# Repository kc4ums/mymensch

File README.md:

# MyMENSCH APRS

A software TNC for WDC's MyMENSCH Rev-C board and a Kenwood TM-V71A. The MyMENSCH does all the packet work itself, with no external TNC: it builds APRS packets and sends them as 1200-baud audio through a small interface board on the radio's data port. The board's FPGA runs a W65C02 at 3.6864 MHz.

## Status

| Part | State |
|---|---|
| Transmit (`tnc/`): position beacons, periodic beacon, test tones, LEDs | Done. Passes the emulator test, including decoding its own audio. **Not yet tried on the board or on air.** |
| Radio interface: schematic and milled PCB (`hardware/`) | Done. The layout passes its clearance and connectivity checks. **Not yet cut.** |
| Receive: demodulate 1200-baud audio, decode packets | Next. The APRS decoder is ready in `tnc/aprs_decode/`. |
| Board hardware facts | Measured; see below. |
| W65C134SXB port (`tnc134/`) | **Runs on a real SXB**, loaded with `tools/sxb134`. It has a test mode (`T`) that prints 20 simulated South Georgia stations. Not yet on air. |
| Uploader (`tools/sxb134/`) | **Works on a real SXB** for loading RAM. Flash writing has been tested only on the emulator; the chip's ID was read on the board. |
| Text map (`tools/aprsmap/`) | **Works with the real SXB** in `tnc134`'s test mode. It can load the TNC itself (`--load`) and has a command line for TNC keys. |
| AMTOR station (`amtor/`) | Written for the W65C134SXB with a PS/2 keyboard, an LCD and a TS-480. Emulator only; its full test still has to be rerun. |

## Folders

| Folder | Contents |
|---|---|
| `tnc/` | The software TNC (transmit side). `tnc/aprs_decode/` holds the APRS decoder from the old PK-232 receiver, for the receive work. |
| `tnc134/` | The same software TNC ported to WDC's W65C134SXB: Port 5 I/O, the ROM monitor's console, 5 V. Includes the South Georgia test mode (`mk_sim.py`). |
| `amtor/` | An HF AMTOR (SITOR-B) message station for the W65C134SXB that needs no PC: a PS/2 keyboard, a 20x4 LCD and a Kenwood TS-480. It can be written into the SXB's flash so it starts at power-up. |
| `hardware/` | Radio interface schematic (`radio_interface.svg`), plus `pcb/`: the CNC-milled board's GRBL G-code, drawings and generator. |
| `hardware/c02board/` | C02COMM: an all-through-hole W65C02S board for these projects (RAM, flash, 2 VIAs, ACIA, two radio ports, LCD, PS/2, USB serial). It's a KiCad 10 project generated from `board.py`. Routed, DRC clean, Gerbers generated; not yet ordered or built. |
| `monitor/` | MMON, a machine-language monitor: dump and edit memory and I/O, load S19 files, run code, catch BRKs. |
| `probes/` | Small programs that test the board's hardware, and what they found. |
| `lib/` | `dbg.inc`: register and memory dump helpers to include in any program. |
| `tools/emu/` | The 65C02 emulator of the MyMENSCH that every test runs on. |
| `tools/sxb134/` | `sxb134.py`: loads, verifies and starts programs on a W65C134SXB through its ROM monitor (instead of EasySXB). It can also write the SXB's SST39SF010A flash (`--flash`). |
| `tools/aprsmap/` | `aprsmap.py`: APRS stations on an ASCII map in a text terminal, from a serial TNC, KISS, or Direwolf over TCP. It can load `tnc134` onto the SXB (`--load`), and `:` opens a command line to the TNC. |
| `docs/` | W65C165i1M08SA datasheet. |

## Building and loading

You need WDCTools (`C:\WDC\Tools\BIN` on the PATH) and WDC's uploader. Each program folder has a `mk_*.bat`.

For the W65C134SXB, use this repo's uploader instead (see `tools/sxb134/README.md`), or let the map load the TNC and start it:

```
python tools\sxb134\sxb134.py COM5 tnc134\tnc134.hex --go 2000 --term
python tools\aprsmap\aprsmap.py COM5 --load --send T --home 31.45,-83.51
```

For the MyMENSCH:

```
cd tnc
mk_tnc.bat
wdc_uploader_term.exe -d COM4 tnc.bin -m write -x -s 5 -t
```

Press RESET on the board when the uploader asks. The program then runs from RAM and its console appears in the uploader's terminal (Ctrl+] to quit). Programs live in RAM, so re-upload after every power cycle. Storing to flash (`-k`) fails on this board with "Clear Failed": the user-flash controller seems to be missing from the FPGA image (see below).

## First bench test (no radio)

1. Load `tnc.bin` as above. LED 0 should double-flash once a second. That shows Timer 1 and the program are running.
2. Press `1` for a test tone. J3-35 (PTT) should go high, and J3-37…43 (the DAC) should toggle. Any key stops it.
3. Then build the interface board (`hardware/pcb/README.md`) and follow "First time on the air" in `tnc/README.md`.

## Wiring to the MyMENSCH

Everything connects to **J3** (VIA_A port A):

| J3 pin | Signal |
|---|---|
| 29 | PA7: comparator output (RX audio) |
| 33 | PA5: radio SQC (optional) |
| 35 | PA4: PTT |
| 37, 39, 41, 43 | PA3-PA0: DAC bits 3-0 |
| 49 | +3V3 |
| 50 | GND |

On J3, pin 49 is +3V3 and pin 50 is GND, the reverse of J4.

## Tests

Every program has an emulator test; none needs the board:

```
python tnc/test_tnc.py
python tnc134/test_tnc134.py
python tools/sxb134/test_sxb134.py
python tools/sxb134/test_flash134.py
python tools/aprsmap/test_aprsmap.py
python amtor/test_amtor.py             (slow and memory-hungry; close other programs first)
python tnc/aprs_decode/run_tests.py
python monitor/test_mmon.py
python probes/test/test_regmap.py      (also test_probe, test_adcprobe, test_dbgdemo)
```

## What this board's FPGA image actually has

These were measured with the programs in `probes/`. They differ from the datasheet:

- **CPU clock:** 3.6864 MHz (the 14.7456 MHz oscillator divided by 4), with standard 65C02 cycle timing.
- **VIA_A:** works, with its ports on J3. **VIA_B and VIA_C are missing.**
- **VIA_A Timer 1 flag:** clears only when `$40` is written to the IFR, not when T1C-L is read.
- **Missing blocks:** the ADC, the multipliers and the chip ID are not in the image. That's why receive uses a comparator instead of the ADC.
- **User flash (UFM):** its registers at `$7FE0-$7FEC` read `00` (the write-protect register should reset to `1F`), and the uploader's `-k` fails with "Clear Failed". So it's most likely missing too, and programs can't be stored in flash.

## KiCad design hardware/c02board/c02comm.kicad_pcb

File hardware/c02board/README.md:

# C02COMM: a through-hole W65C02S board for the radio projects

This is a single board computer for the APRS TNC and the AMTOR station: a WDC W65C02S, RAM, flash, two radio ports, an LCD and keyboard connection, and USB serial to a PC. **Every part is through-hole** and every chip sits in a socket, so it can be built and repaired with a soldering iron. The PCB is a 2-layer **185 × 125 mm** board to order from JLCPCB, PCBWay or similar.

**Status: routed, DRC clean, Gerbers ready.** Placement, schematic, netlist and routing are done. KiCad's DRC shows 0 errors and 0 unconnected pads. `python mk_fab.py` writes `fab/c02comm_gerbers.zip` (not committed; regenerate it). The clock oscillator X1 drives PHI2 through R44 (33 ohm), 7 mm from its output pin. Nothing has been built.

## What's on it

| Block | Parts | Notes |
|---|---|---|
| CPU | W65C02S, 3.6864 MHz oscillator | The same clock as the existing TNC and AMTOR code. The oscillator is socketed: change it to change the speed. It drives PHI2 through R44 (33 ohm), which damps ringing on the long clock track. |
| RAM | AS6C62256, 32 KB | `$0000-$7EFF` |
| Flash | SST39SF010A, 128 KB | The same chip as on the W65C134SXB. `$8000-$FFFF` shows one of four 32 KB banks. JP1 write-protects it. |
| VIA1 | W65C22N | The two radio ports |
| VIA2 | W65C22N | 20x4 LCD, PS/2 keyboard, flash bank select, 4 LEDs |
| ACIA | W65C51N, 1.8432 MHz oscillator | Serial to a plug-in USB module (FTDI or CH340, 5 V) |
| Radio ports ×2 | LM393, 2N7000, R-2R DAC | The same circuit as `../radio_interface.svg`, already proven with the TNC |
| Reset | DS1813 | Clean power-on reset, plus a RESET and an NMI button |
| Power | 1N5819, LM7805 | 9-15 V in on a screw terminal, so 13.8 V from the radio supply is fine |

## Memory map

| Address | What |
|---|---|
| `$0000-$7EFF` | RAM |
| `$7F00-$7F0F` | VIA1 (radios) |
| `$7F10-$7F1F` | VIA2 (LCD, keyboard, bank, LEDs) |
| `$7F20-$7F2F` | ACIA |
| `$7F30`, `$7F40`, `$7F50` | `/CS3`, `/CS4`, `/CS5` on the I/O header, 16 bytes each |
| `$7F60-$7FFF` | free |
| `$8000-$FFFF` | flash bank 0-3 (VIA2 PA6 = A15, PA7 = A16) |

- **Bank at reset:** the bank lines are pulled low, so bank 0 is selected and the reset vector comes from bank 0.
- **Writing the flash:** writes use the same command sequence as `../../tools/sxb134/flash134.asm` (`$D555` / `$AAAA`), running from RAM.
- **Decoding:** a 74HC00, a 74HC30 and a 74HC138. `check_board.py` simulates the decoding for all 65536 addresses.

## Port pins

**VIA1 (`$7F00`).** Radio 1 is wired exactly like the MyMENSCH's VIA_A port A, so the TNC code needs only new addresses:

| Pin | Radio 1 (port A) | Radio 2 (port B) |
|---|---|---|
| P0-P3 | DAC bits 0-3 | DAC bits 0-3 |
| P4 | PTT (and the red TX1 LED) | PTT (TX2 LED) |
| P5 | SQC from the radio | SQC |
| P6 | spare, on the I/O header | spare, on the I/O header |
| P7 | comparator (RX audio) | comparator |
| CA1 / CB1 | the same comparator, for edge interrupts | the same comparator |

**VIA2 (`$7F10`):**

| Pin | Use |
|---|---|
| PA0-PA3 | LCD D4-D7 |
| PA4 / PA5 | LCD RS / E (R/W is tied low) |
| PA6 / PA7 | flash A15 / A16 (bank) |
| PB0-PB3 | LED0-LED3 (lit when high) |
| PB4 | PS/2 data (a port pin, so its level can be read) |
| PB5-PB7, CA2, CB1, CB2 | I/O header |
| CA1 | PS/2 clock (interrupt on the falling edge) |

**Interrupts:** `/IRQ` is shared by VIA1, VIA2 and the ACIA, with a 3.3k pull-up. That's why both VIAs must be the **W65C22N** (open-drain IRQ), **not the W65C22S**, whose IRQ output is push-pull.

## Connectors

| Ref | Connector | Pins |
|---|---|---|
| J1 | 2-way screw terminal | 1 = +9-15 V, 2 = GND. A reversed supply is blocked by D1. |
| J7, J8 | 5-way screw terminal, one per radio | 1 ANI, 2 GND, 3 PTT, 4 ANO, 5 SQC |
| J3 | 1x16 header | HD44780 LCD in its own pin order (VSS VDD V0 RS RW E D0-D7 A K). RV3 sets the contrast. |
| J4 | 1x4 header | PS/2 socket breakout: +5V GND CLK DATA |
| J5 | 1x6 header | USB-serial module, FTDI order: GND CTS VCC TXD RXD RTS |
| J6 | 2x10 header | +5V, GND, the spare VIA lines, `/CS3-5`, `/IRQ`, `/RES`, PHI2, R/W |
| JP1 | 3-pin jumper | flash write: 1-2 = writable, 2-3 = protected |
| JP2 | 2-pin jumper | powers the board from the USB module. Fit it **only** when nothing is on J1. |

**Radio cable:** use a 6-pin mini-DIN male cable (a cut PS/2 extension cable works) wired to the terminal. The pin numbers are the TS-480 / TM-V71A data port's:

| Terminal | Data port pin | Signal |
|---|---|---|
| 1 ANI | 1 | audio into the radio |
| 2 GND | 2 | ground |
| 3 PTT | 3 | PTT (pulled to ground by the 2N7000) |
| 4 ANO | 5 | audio out of the radio |
| 5 SQC | 6 | squelch / busy |

Pin 4 isn't used. Check the cable's colours with an ohmmeter, because PS/2 cables differ.

## Building it

- **Sockets:** put every DIP chip in a socket. The chips are 0.6" wide for the CPU, RAM, flash, VIAs and ACIA, and 0.3" for the logic and the LM393. The oscillators are **half-size (8-pin DIP) cans** in 8-pin sockets. Full-size 14-pin cans such as the ECS-100AX do not fit. A ZIF socket for the flash is handy if you reflash it out of circuit.
- **Do not fit R121 and R221.** They are the 20k SQC dividers for a 3.3 V board, marked DNP on the board.
- **LM7805 heat:** at 13.8 V in and about 200 mA with the LCD backlight on, the LM7805 dissipates around 2 W. Fit a clip-on TO-220 heatsink.
- **Setting the audio level:** set RV1 / RV2 (TX audio level) with the radio on a dummy load, as in `../../tnc/README.md`.
- **ACIA bug:** the W65C51N's "transmit register empty" bit is stuck on, a known silicon bug. Send with a delay of one character time (about 1.04 ms at 9600 baud) instead of polling it.

Parts are listed in `bom.csv`, written by `python mk_fab.py --bom` from the `BUY` table in `board.py`. Each line has a manufacturer part number, and a Mouser number where one was confirmed (Nov 2026). To order, upload `bom.csv` to Mouser's BOM tool (mouser.com/bom). It matches the manufacturer part numbers, including on lines with no Mouser number. The last rows are parts that aren't on the PCB: sockets, heatsink, jumpers, LCD, PS/2 breakout and USB module.

## Files

| File | What it is |
|---|---|
| `board.py` | **The design.** Every part, footprint, position and pin-to-net connection. Edit this, then regenerate everything else. |
| `check_board.py` | Plain Python. Checks the design (see below). |
| `mk_pcb.py` | Run with KiCad's Python. Builds `c02comm.kicad_pcb`: placement, nets, ground planes on both layers, design rules. It also writes `c02comm.dsn` for the autorouter, and imports `c02comm.ses` (the routed tracks) when it exists. |
| `mk_sch.py` | Writes `c02comm.kicad_sch` and the `c02` symbol library. Chips are drawn by their DIP pinout, with a net label on every pin. |
| `check_place.py` | KiCad Python. Checks that no courtyards overlap and that all parts are on the board, and draws `place.png`. |
| `mk_fab.py` | Routes (optionally), runs DRC, writes the Gerber zip in `fab/`, and writes `bom.csv`. |
| `c02comm.kicad_pro/.kicad_pcb/.kicad_sch` | The KiCad 10 project; open it in KiCad to look around. |

Regenerate after editing `board.py`:

```
python check_board.py
python mk_sch.py
"C:\Program Files\KiCad\10.0\bin\python.exe" mk_pcb.py
"C:\Program Files\KiCad\10.0\bin\python.exe" check_place.py png
```

## Checks

`check_board.py` passes all of these:
- **Nets and pins:** every net joins at least two pins, and every chip lists all its pins.
- **Chip pinouts:** power and ground are on each chip's datasheet pins, and every chip has a decoupling capacitor.
- **Buses:** the CPU's address and data lines reach the right pins of the RAM, flash, both VIAs and the ACIA.
- **Decoding:** the gate network, simulated from the netlist, matches the memory map for every address. Exactly one chip is selected at a time.
- **Strobes:** `/RD` happens only on reads and `/WR` only on writes, and both only while PHI2 is high.
- **Radio ports:** both are wired the same way, and the DAC bit order and the 2N7000 orientation are right.
- **Keyboard and interrupts:** the PS/2, LCD, interrupt and serial wiring are right.

In KiCad:
- **ERC:** 0 violations.
- **Schematic against board:** the schematic's netlist, exported by KiCad, has the same 129 nets, pin for pin, as `board.py` and the PCB.
- **DRC (unrouted):** no clearance or edge errors. All that's left is the 319 connections waiting for tracks, plus cosmetic silkscreen overlaps of reference text.

## Routing

The board has 319 connections, mostly the address and data buses. They are routed with **Freerouting 2.5.0**, installed from its official MSI at `C:\Users\kc4um\AppData\Local\freerouting\`. Its usage statistics are turned off in `%APPDATA%\freerouting\freerouting.json` (`allow_telemetry: false`, `disable_analytics: true`).

### Where it stands (2026-11-19)

**Run 1: every connection routed, but it failed KiCad's DRC.** Freerouting left GND for the copper planes to connect. On this board the bus tracks cut the planes into islands, so 13 GND pins were left isolated, among them pins on U1, U2, U8 and U9.

**Fix, in `mk_pcb.py`:**
- **GND as tracks:** GND is now routed as ordinary tracks, and the two ground planes are added only after the tracks are imported, as extra copper.
- **Rules:** the minimum track is 0.15 mm, where Freerouting narrows tracks into pads. Copper may come within 0.3 mm of the edge, which board houses allow.
- **Thermals:** `c02comm.kicad_dru` allows a thermal relief with a single spoke, since every GND pin also has its own track.

**Run 2: all 319 connections routed with 0 violations after 11 passes, but no result saved.** Claude Code stopped the run in Freerouting's final "optimizer" stage, because the PC was low on memory. `mk_fab.py` now runs Freerouting with `-mt 2` (2 threads) to use less memory.

**Run 3 (2026-11-19): all 319 connections routed, 0 unconnected pads.** The optimizer pass made the score worse and was rejected, so the router's result was kept. `drc.txt` lists 6 `starved_thermal` errors: GND pads on Q1, Q2, U5, J6 and R41 whose thermal spokes reach only an isolated island of the plane. Every one of these pads also has its own GND track, so they are connected. **Fixed:** KiCad ignored the one-spoke rule in `c02comm.kicad_dru` and used the board's default minimum of 2 spokes. `mk_pcb.py` now sets `min_resolved_spokes: 1` in the project's board rules. With that, the DRC shows 0 errors, and `mk_fab.py` wrote the Gerbers.

**Run 4 (2026-11-19):** re-routed after moving the PS/2 data line to PB4. All connections routed. With the one-spoke thermal setting, the DRC shows 0 errors and 0 unconnected pads.

**Run 5 (2026-11-19):** re-routed after adding R44, the PHI2 series resistor. DRC 0 errors, 0 unconnected pads. The X1-to-R44 track is 7 mm; the PHI2 track after R44 is 267 mm.

### To re-route

After a reboot, with little else open, run this from **a normal PowerShell window**, not inside Claude Code. That way nothing stops it for using memory. It takes about 20-35 minutes.

```
cd C:\Projects\mymensch\hardware\c02board
python mk_fab.py --route C:\Users\kc4um\AppData\Local\freerouting\freerouting.exe
```

It does these steps in order:
1. Exports `c02comm.dsn`.
2. Routes it into `c02comm.ses`.
3. Rebuilds the board with the tracks and ground planes.
4. Runs KiCad's DRC. The report goes to `drc.txt`.
5. If the DRC is clean, writes `fab/c02comm_gerbers.zip` and `bom.csv`.

The routing log is printed on screen.

**If you'd rather route it another way:** install "Freerouting" in KiCad's Plugin and Content Manager and run it on `c02comm.kicad_pcb`, or route it by hand in KiCad. Either way, add the GND planes afterwards (`mk_pcb.py` does this when `c02comm.ses` exists), then run `python mk_fab.py`.

**After routing:**
1. Check the DRC result.
2. Fill the zones (B).
3. Look over the board, especially the PHI2 track. Keep it short.
4. Upload `fab/c02comm_gerbers.zip` to the board house: 2 layers, 1.6 mm, HASL. Any colour.

**Design rules** suit any 2-layer "standard" service:
- 0.2 mm clearance;
- 0.3 mm signal tracks and 0.8 mm power tracks;
- 0.8 / 0.4 mm vias;
- 0.5 mm copper-to-edge;
- ground plane on both layers.

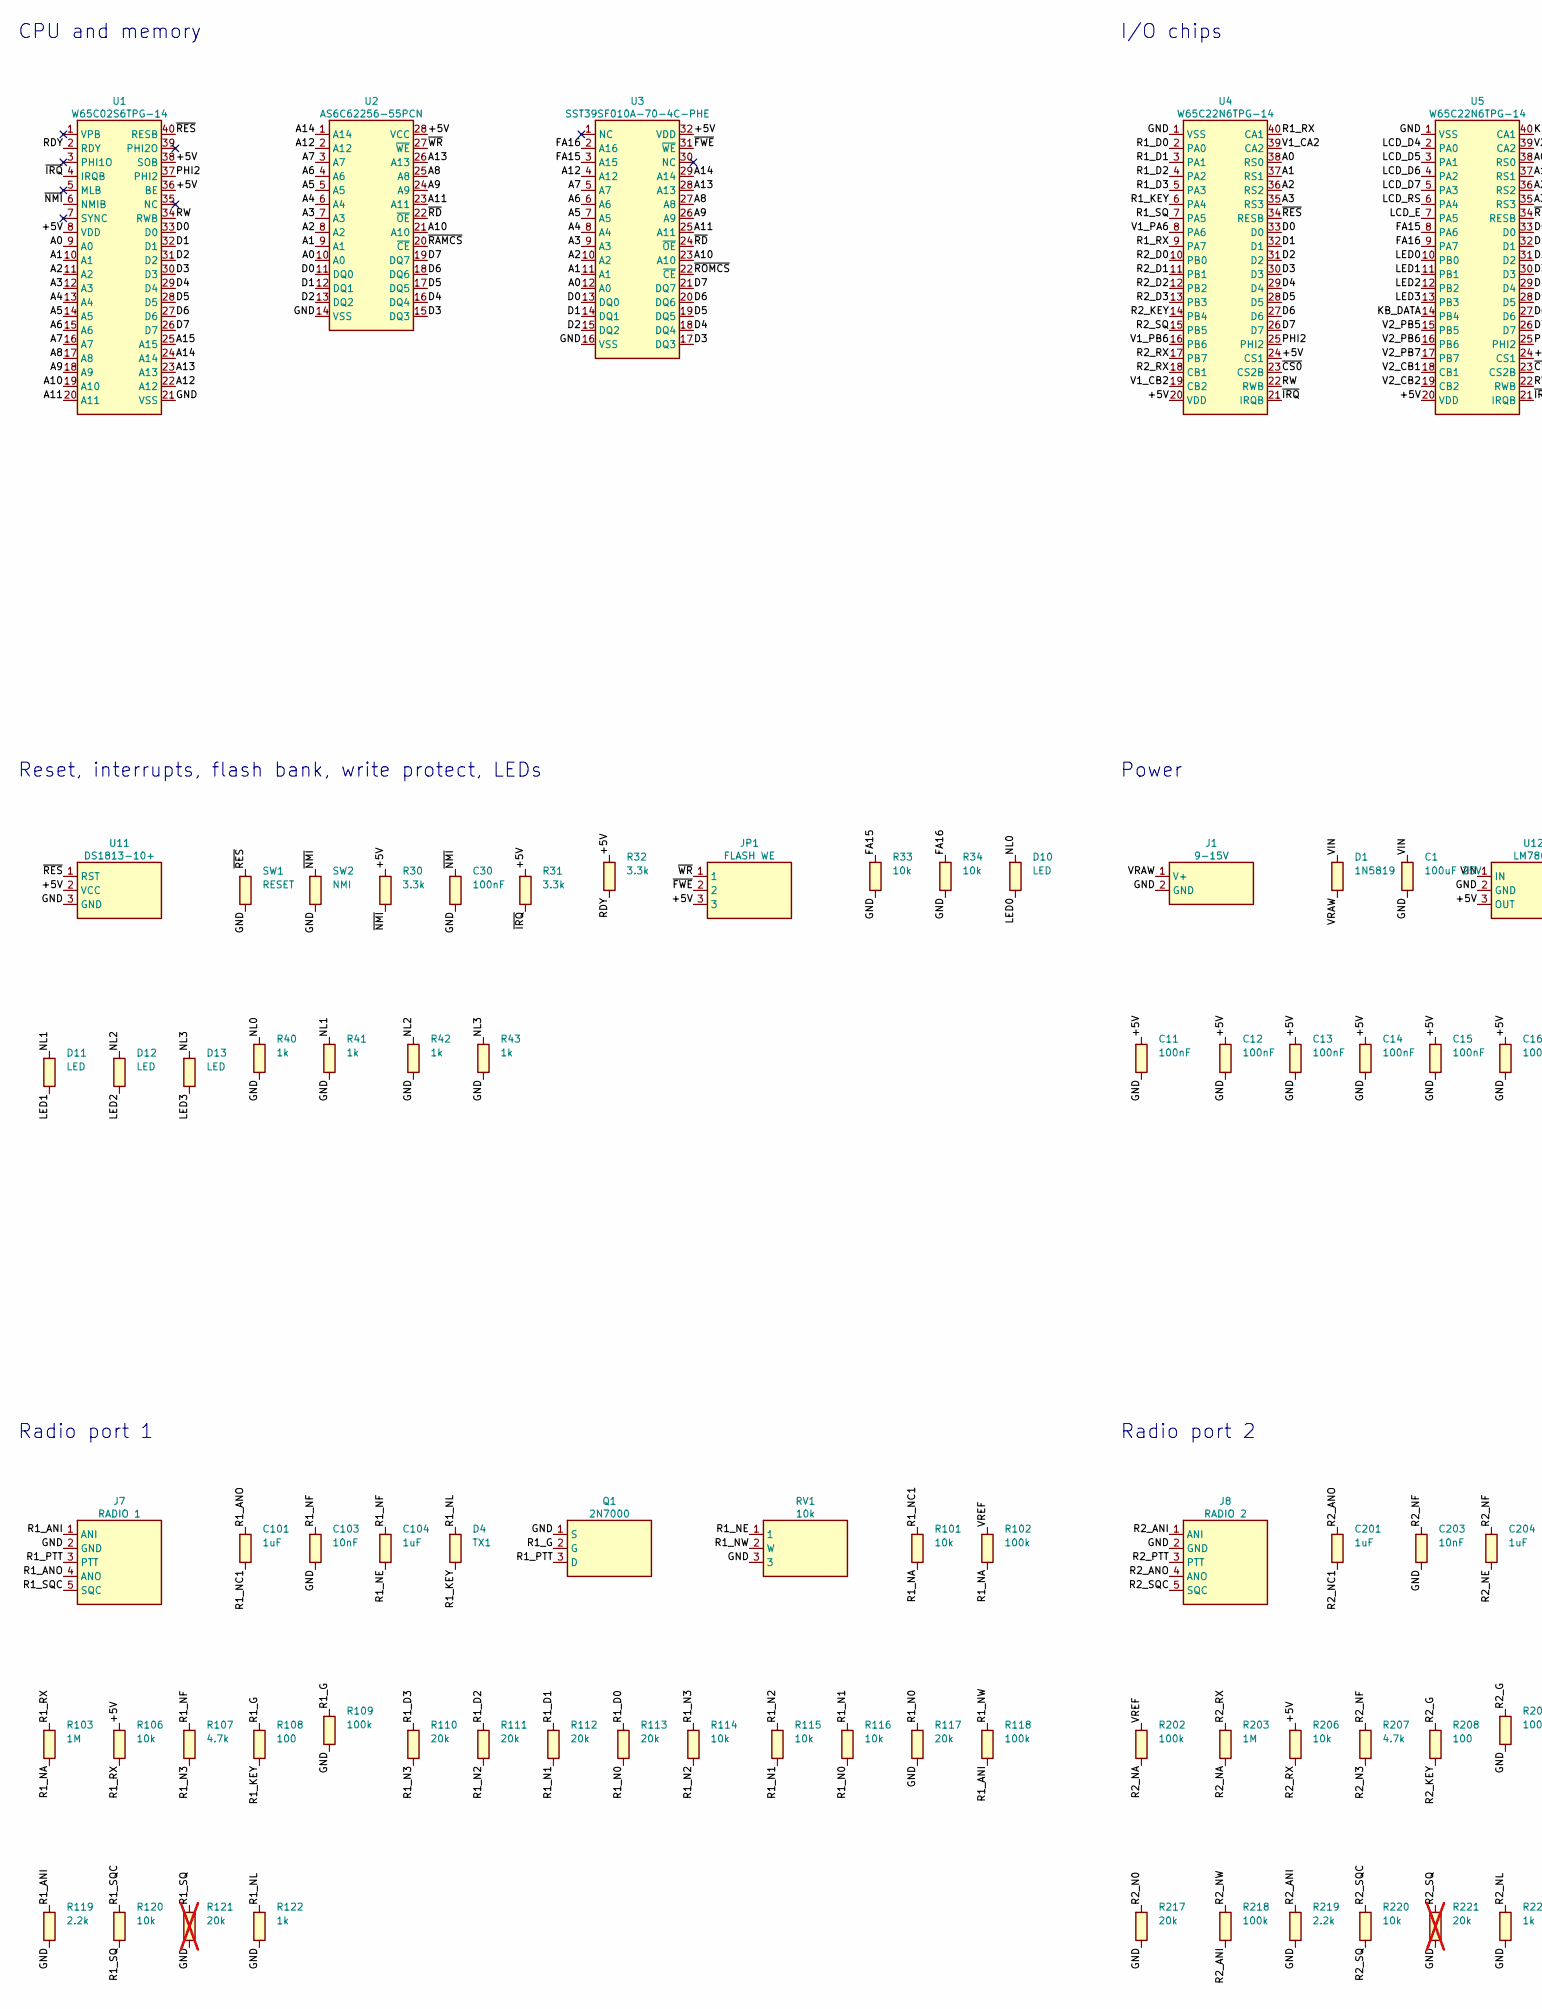
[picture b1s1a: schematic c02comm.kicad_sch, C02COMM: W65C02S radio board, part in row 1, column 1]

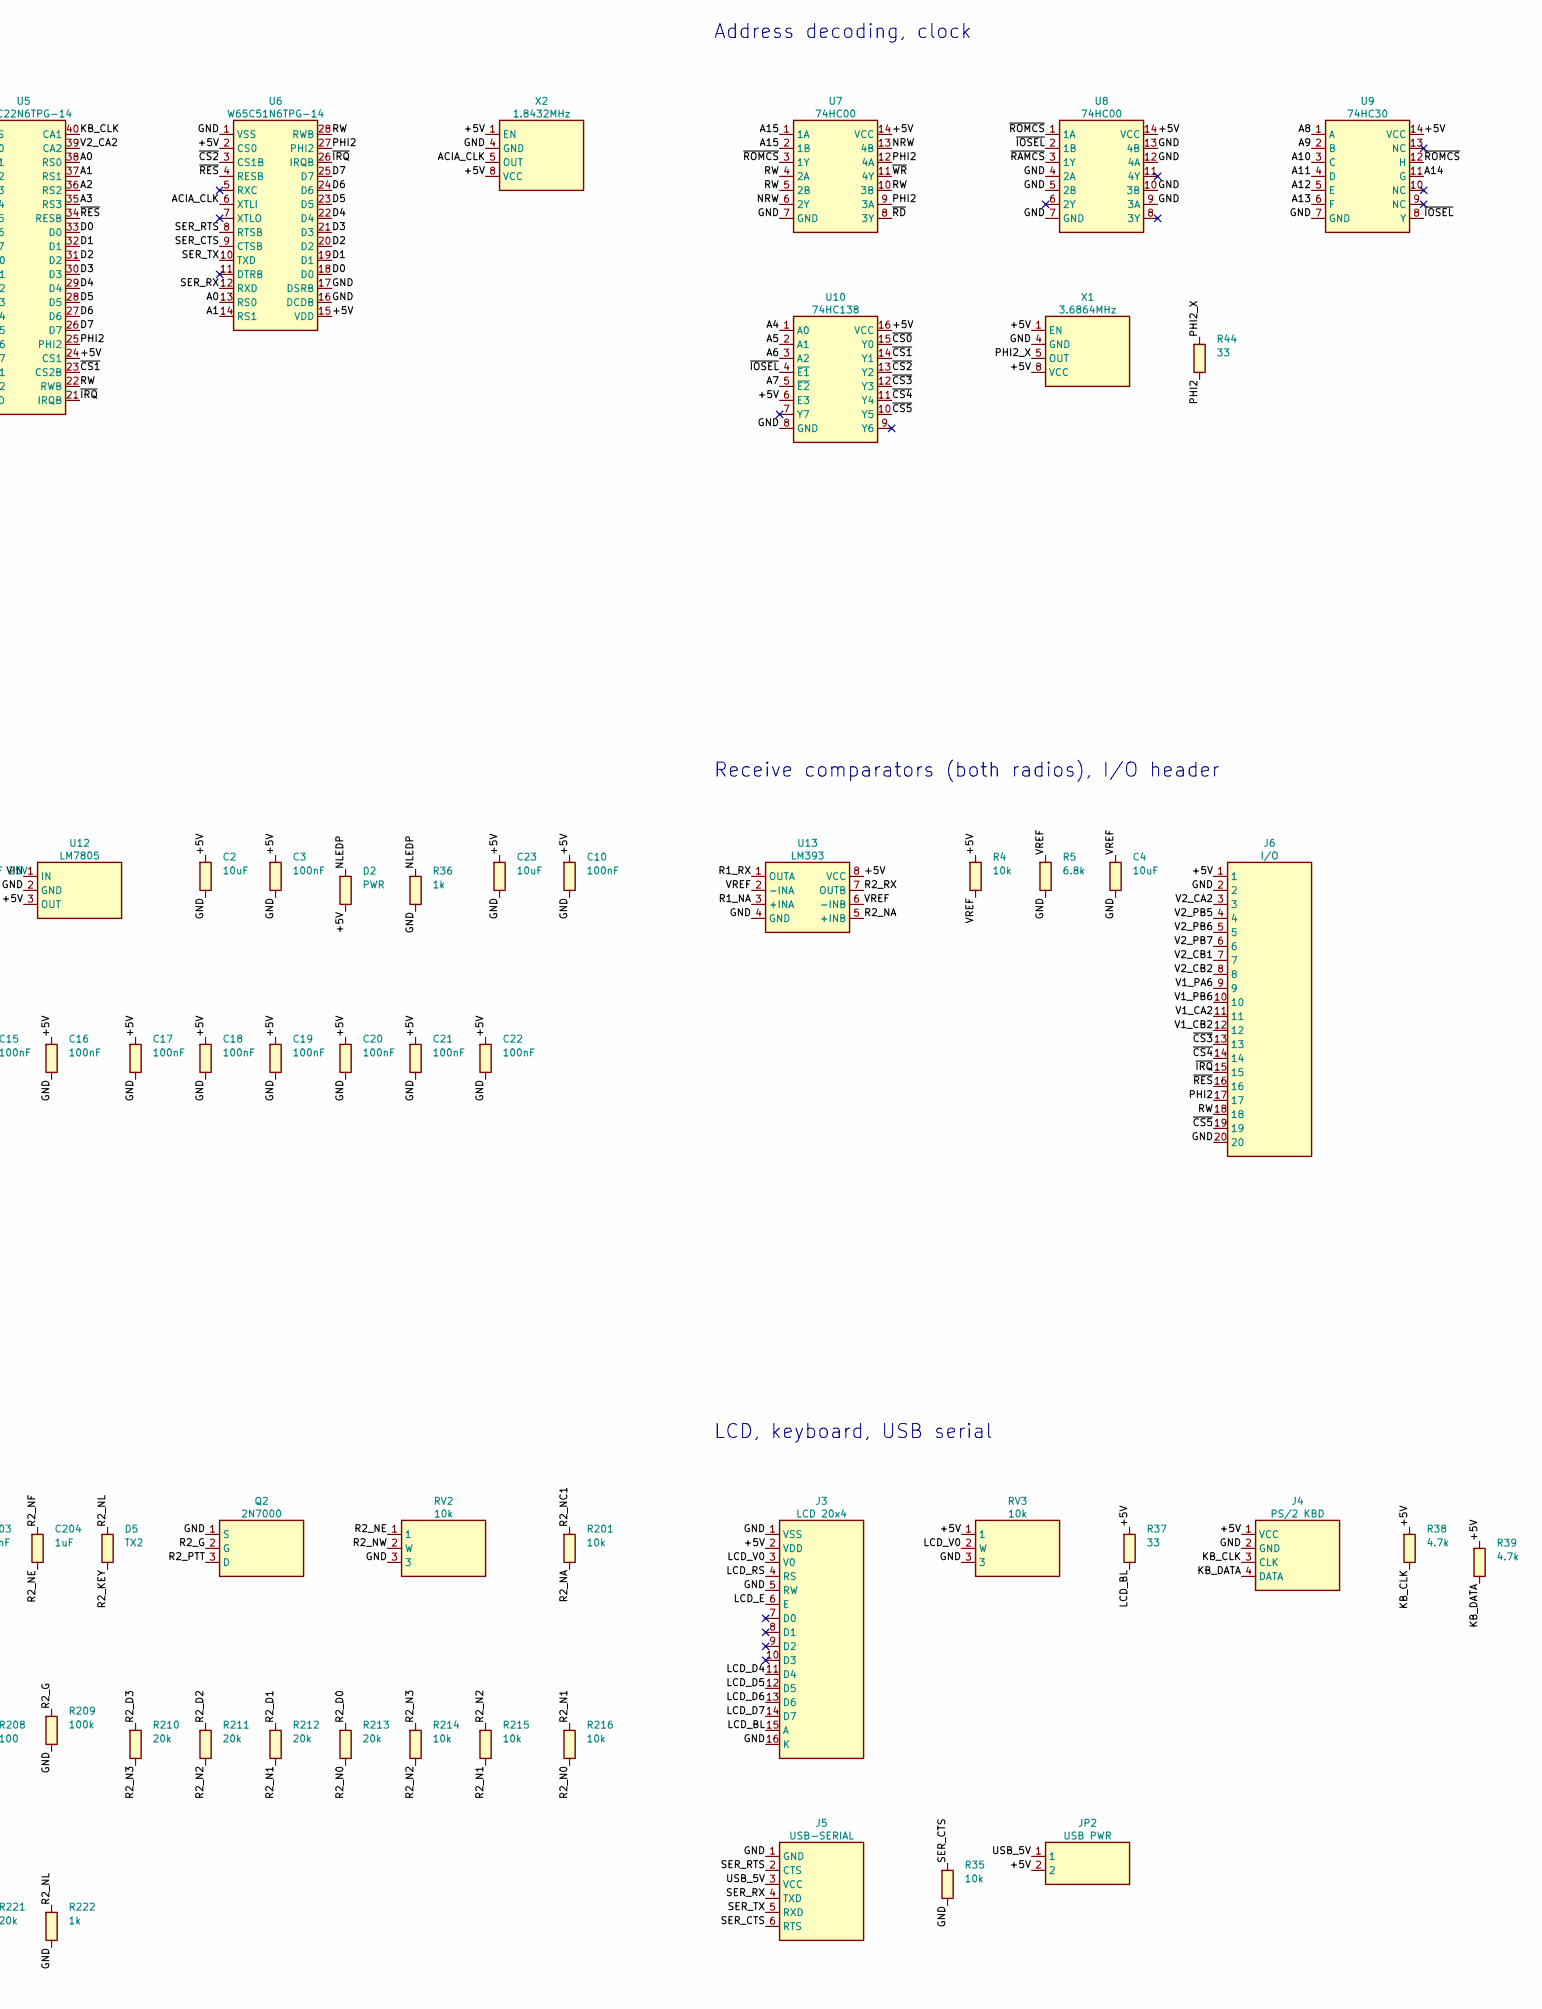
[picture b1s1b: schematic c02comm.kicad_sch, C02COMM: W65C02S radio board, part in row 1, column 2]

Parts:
C1: 100uF 25V; CP_Radial_D8.0mm_P3.50mm
C2, C4, C23: 10uF; CP_Radial_D5.0mm_P2.00mm
C3, C10, C11, C12, C13, C14, C15, C16, C17, C18, C19, C20, C21, C22, C30: 100nF; C_Disc_D5.0mm_W2.5mm_P5.00mm
C101, C104, C201, C204: 1uF; C_Disc_D5.0mm_W2.5mm_P5.00mm
C103, C203: 10nF; C_Disc_D5.0mm_W2.5mm_P5.00mm
D1: 1N5819; D_DO-41_SOD81_P10.16mm_Horizontal
D2: PWR; LED_D3.0mm; MPN 3 mm LED, green
D4: TX1; LED_D3.0mm; MPN 3 mm LED, red
D5: TX2; LED_D3.0mm; MPN 3 mm LED, red
D10, D11, D12, D13: LED; LED_D3.0mm; MPN 3 mm LED
J1: 9-15V; TerminalBlock_Phoenix_MKDS-1,5-2_1x02_P5.00mm_Horizontal; MPN Phoenix MKDS 1,5/2 or any 5 mm screw te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
J3: LCD 20x4; PinHeader_1x16_P2.54mm_Vertical
J4: PS/2 KBD; PinHeader_1x04_P2.54mm_Vertical
J5: USB-SERIAL; PinHeader_1x06_P2.54mm_Vertical
J6: I/O; PinHeader_2x10_P2.54mm_Vertical
J7: RADIO 1; TerminalBlock_Phoenix_MKDS-1,5-5_1x05_P5.00mm_Horizontal; MPN 5 mm 5-way screw terminal
J8: RADIO 2; TerminalBlock_Phoenix_MKDS-1,5-5_1x05_P5.00mm_Horizontal; MPN 5 mm 5-way screw terminal
JP1: FLASH WE; PinHeader_1x03_P2.54mm_Vertical
JP2: USB PWR; PinHeader_1x02_P2.54mm_Vertical
Q1, Q2: 2N7000; TO-92_Inline_Wide; MPN 2N7000 (TO-92)
R4, R33, R34, R35, R101, R106, R114, R115, R116, R120, R201, R206, R214, R215, R216, R220: 10k; R_Axial_DIN0207_L6.3mm_D2.5mm_P10.16mm_Horizontal
R5: 6.8k; R_Axial_DIN0207_L6.3mm_D2.5mm_P10.16mm_Horizontal
R30, R31, R32: 3.3k; R_Axial_DIN0207_L6.3mm_D2.5mm_P10.16mm_Horizontal
R36, R40, R41, R42, R43, R122, R222: 1k; R_Axial_DIN0207_L6.3mm_D2.5mm_P10.16mm_Horizontal
R37, R44: 33; R_Axial_DIN0207_L6.3mm_D2.5mm_P10.16mm_Horizontal
R38, R39, R107, R207: 4.7k; R_Axial_DIN0207_L6.3mm_D2.5mm_P10.16mm_Horizontal
R102, R109, R118, R202, R209, R218: 100k; R_Axial_DIN0207_L6.3mm_D2.5mm_P10.16mm_Horizontal
R103, R203: 1M; R_Axial_DIN0207_L6.3mm_D2.5mm_P10.16mm_Horizontal
R108, R208: 100; R_Axial_DIN0207_L6.3mm_D2.5mm_P10.16mm_Horizontal
R110, R111, R112, R113, R117, R210, R211, R212, R213, R217: 20k; R_Axial_DIN0207_L6.3mm_D2.5mm_P10.16mm_Horizontal
R119, R219: 2.2k; R_Axial_DIN0207_L6.3mm_D2.5mm_P10.16mm_Horizontal
R121, R221: 20k; R_Axial_DIN0207_L6.3mm_D2.5mm_P10.16mm_Horizontal; not fitted
RV1, RV2, RV3: 10k; Potentiometer_Bourns_3296W_Vertical
SW1: RESET; SW_PUSH_6mm; MPN 6 mm tactile switch
SW2: NMI; SW_PUSH_6mm; MPN 6 mm tactile switch
U1: W65C02S6TPG-14; DIP-40_W15.24mm_Socket; MPN WDC W65C02S6TPG-14
U2: AS6C62256-55PCN; DIP-28_W15.24mm_Socket; MPN Alliance AS6C62256-55PCN
U3: SST39SF010A-70-4C-PHE; DIP-32_W15.24mm_Socket; MPN Microchip SST39SF010A-70-4C-PHE
U4, U5: W65C22N6TPG-14; DIP-40_W15.24mm_Socket; MPN WDC W65C22N6TPG-14 (N = open-drain IRQ)
U6: W65C51N6TPG-14; DIP-28_W15.24mm_Socket; MPN WDC W65C51N6TPG-14
U7, U8: 74HC00; DIP-14_W7.62mm_Socket; MPN 74HC00 (TI SN74HC00N)
U9: 74HC30; DIP-14_W7.62mm_Socket; MPN 74HC30 (TI SN74HC30N)
U10: 74HC138; DIP-16_W7.62mm_Socket; MPN 74HC138 (TI SN74HC138N)
U11: DS1813-10+; TO-92_Inline_Wide; MPN Analog Devices DS1813-10+
U12: LM7805; TO-220-3_Vertical; MPN LM7805 (TO-220) with a clip-on heatsink
U13: LM393; DIP-8_W7.62mm_Socket; MPN LM393P (TI) or any LM393 DIP-8
X1: 3.6864MHz; Oscillator_DIP-8; MPN any 5 V HCMOS half-size (8-pin DIP) can
X2: 1.8432MHz; Oscillator_DIP-8; MPN any 5 V HCMOS half-size (8-pin DIP) can

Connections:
+5V: C2.1 (+), C3.1, C10.1, C11.1, C12.1, C13.1, C14.1, C15.1, C16.1, C17.1, C18.1, C19.1, C20.1, C21.1, C22.1, C23.1 (+), D2.2 (A), J3.2 (VDD), J4.1 (VCC), J6.1, JP1.3, JP2.2, R4.1, R30.1, R31.1, R32.1, R37.1, R38.1, R39.1, R106.1, R206.1, RV3.1, U1.8 (VDD), U1.36 (BE), U1.38 (SOB), U2.28 (VCC), U3.32 (VDD), U4.20 (VDD), U4.24 (CS1), U5.20 (VDD), U5.24 (CS1), U6.2 (CS0), U6.15 (VDD), U7.14 (VCC), U8.14 (VCC), U9.14 (VCC), U10.6 (E3), U10.16 (VCC), U11.2 (VCC), U12.3 (OUT), U13.8 (VCC), X1.1 (EN), X1.8 (VCC), X2.1 (EN), X2.8 (VCC)
A0: U1.9 (A0), U2.10 (A0), U3.12 (A0), U4.38 (RS0), U5.38 (RS0), U6.13 (RS0)
A1: U1.10 (A1), U2.9 (A1), U3.11 (A1), U4.37 (RS1), U5.37 (RS1), U6.14 (RS1)
A2: U1.11 (A2), U2.8 (A2), U3.10 (A2), U4.36 (RS2), U5.36 (RS2)
A3: U1.12 (A3), U2.7 (A3), U3.9 (A3), U4.35 (RS3), U5.35 (RS3)
A4: U1.13 (A4), U2.6 (A4), U3.8 (A4), U10.1 (A0)
A5: U1.14 (A5), U2.5 (A5), U3.7 (A5), U10.2 (A1)
A6: U1.15 (A6), U2.4 (A6), U3.6 (A6), U10.3 (A2)
A7: U1.16 (A7), U2.3 (A7), U3.5 (A7), U10.5 (~E2)
A8: U1.17 (A8), U2.25 (A8), U3.27 (A8), U9.1 (A)
A9: U1.18 (A9), U2.24 (A9), U3.26 (A9), U9.2 (B)
A10: U1.19 (A10), U2.21 (A10), U3.23 (A10), U9.3 (C)
A11: U1.20 (A11), U2.23 (A11), U3.25 (A11), U9.4 (D)
A12: U1.22 (A12), U2.2 (A12), U3.4 (A12), U9.5 (E)
A13: U1.23 (A13), U2.26 (A13), U3.28 (A13), U9.6 (F)
A14: U1.24 (A14), U2.1 (A14), U3.29 (A14), U9.11 (G)
A15: U1.25 (A15), U7.1 (1A), U7.2 (1B)
ACIA_CLK: U6.6 (XTLI), X2.5 (OUT)
D0: U1.33 (D0), U2.11 (DQ0), U3.13 (DQ0), U4.33 (D0), U5.33 (D0), U6.18 (D0)
D1: U1.32 (D1), U2.12 (DQ1), U3.14 (DQ1), U4.32 (D1), U5.32 (D1), U6.19 (D1)
D2: U1.31 (D2), U2.13 (DQ2), U3.15 (DQ2), U4.31 (D2), U5.31 (D2), U6.20 (D2)
D3: U1.30 (D3), U2.15 (DQ3), U3.17 (DQ3), U4.30 (D3), U5.30 (D3), U6.21 (D3)
D4: U1.29 (D4), U2.16 (DQ4), U3.18 (DQ4), U4.29 (D4), U5.29 (D4), U6.22 (D4)
D5: U1.28 (D5), U2.17 (DQ5), U3.19 (DQ5), U4.28 (D5), U5.28 (D5), U6.23 (D5)
D6: U1.27 (D6), U2.18 (DQ6), U3.20 (DQ6), U4.27 (D6), U5.27 (D6), U6.24 (D6)
D7: U1.26 (D7), U2.19 (DQ7), U3.21 (DQ7), U4.26 (D7), U5.26 (D7), U6.25 (D7)
FA15: R33.1, U3.3 (A15), U5.8 (PA6)
FA16: R34.1, U3.2 (A16), U5.9 (PA7)
GND: C1.2, C2.2, C3.2, C4.2, C10.2, C11.2, C12.2, C13.2, C14.2, C15.2, C16.2, C17.2, C18.2, C19.2, C20.2, C21.2, C22.2, C23.2, C30.2, C103.2, C203.2, J1.2 (GND), J3.1 (VSS), J3.5 (RW), J3.16 (K), J4.2 (GND), J5.1 (GND), J6.2, J6.20, J7.2 (GND), J8.2 (GND), Q1.1 (S), Q2.1 (S), R5.2, R33.2, R34.2, R35.2, R36.2, R40.2, R41.2, R42.2, R43.2, R109.2, R117.2, R119.2, R121.2, R122.2, R209.2, R217.2, R219.2, R221.2, R222.2, RV1.3, RV2.3, RV3.3, SW1.2, SW2.2, U1.21 (VSS), U2.14 (VSS), U3.16 (VSS), U4.1 (VSS), U5.1 (VSS), U6.1 (VSS), U6.16 (DCDB), U6.17 (DSRB), U7.7 (GND), U8.4 (2A), U8.5 (2B), U8.7 (GND), U8.9 (3A), U8.10 (3B), U8.12 (4A), U8.13 (4B), U9.7 (GND), U10.8 (GND), U11.3 (GND), U12.2 (GND), U13.4 (GND), X1.4 (GND), X2.4 (GND)
KB_CLK: J4.3 (CLK), R38.2, U5.40 (CA1)
KB_DATA: J4.4 (DATA), R39.2, U5.14 (PB4)
LCD_BL: J3.15 (A), R37.2
LCD_D4: J3.11 (D4), U5.2 (PA0)
LCD_D5: J3.12 (D5), U5.3 (PA1)
LCD_D6: J3.13 (D6), U5.4 (PA2)
LCD_D7: J3.14 (D7), U5.5 (PA3)
LCD_E: J3.6 (E), U5.7 (PA5)
LCD_RS: J3.4 (RS), U5.6 (PA4)
LCD_V0: J3.3 (V0), RV3.2 (W)
LED0: D10.2 (A), U5.10 (PB0)
LED1: D11.2 (A), U5.11 (PB1)
LED2: D12.2 (A), U5.12 (PB2)
LED3: D13.2 (A), U5.13 (PB3)
NL0: D10.1 (K), R40.1
NL1: D11.1 (K), R41.1
NL2: D12.1 (K), R42.1
NL3: D13.1 (K), R43.1
NLEDP: D2.1 (K), R36.1
NRW: U7.6 (2Y), U7.13 (4B)
PHI2: J6.17, R44.2, U1.37 (PHI2), U4.25 (PHI2), U5.25 (PHI2), U6.27 (PHI2), U7.9 (3A), U7.12 (4A)
PHI2_X: R44.1, X1.5 (OUT)
R1_ANI: J7.1 (ANI), R118.2, R119.1
R1_ANO: C101.1, J7.4 (ANO)
R1_D0: R113.1, U4.2 (PA0)
R1_D1: R112.1, U4.3 (PA1)
R1_D2: R111.1, U4.4 (PA2)
R1_D3: R110.1, U4.5 (PA3)
R1_G: Q1.2 (G), R108.1, R109.1
R1_KEY: D4.2 (A), R108.2, U4.6 (PA4)
R1_N0: R113.2, R116.2, R117.1
R1_N1: R112.2, R115.2, R116.1
R1_N2: R111.2, R114.2, R115.1
R1_N3: R107.2, R110.2, R114.1
R1_NA: R101.2, R102.2, R103.2, U13.3 (+INA)
R1_NC1: C101.2, R101.1
R1_NE: C104.2, RV1.1
R1_NF: C103.1, C104.1, R107.1
R1_NL: D4.1 (K), R122.1
R1_NW: R118.1, RV1.2 (W)
R1_PTT: J7.3 (PTT), Q1.3 (D)
R1_RX: R103.1, R106.2, U4.9 (PA7), U4.40 (CA1), U13.1 (OUTA)
R1_SQ: R120.2, R121.1, U4.7 (PA5)
R1_SQC: J7.5 (SQC), R120.1
R2_ANI: J8.1 (ANI), R218.2, R219.1
R2_ANO: C201.1, J8.4 (ANO)
R2_D0: R213.1, U4.10 (PB0)
R2_D1: R212.1, U4.11 (PB1)
R2_D2: R211.1, U4.12 (PB2)
R2_D3: R210.1, U4.13 (PB3)
R2_G: Q2.2 (G), R208.1, R209.1
R2_KEY: D5.2 (A), R208.2, U4.14 (PB4)
R2_N0: R213.2, R216.2, R217.1
R2_N1: R212.2, R215.2, R216.1
R2_N2: R211.2, R214.2, R215.1
R2_N3: R207.2, R210.2, R214.1
R2_NA: R201.2, R202.2, R203.2, U13.5 (+INB)
R2_NC1: C201.2, R201.1
R2_NE: C204.2, RV2.1
R2_NF: C203.1, C204.1, R207.1
R2_NL: D5.1 (K), R222.1
R2_NW: R218.1, RV2.2 (W)
R2_PTT: J8.3 (PTT), Q2.3 (D)
R2_RX: R203.1, R206.2, U4.17 (PB7), U4.18 (CB1), U13.7 (OUTB)
R2_SQ: R220.2, R221.1, U4.15 (PB5)
R2_SQC: J8.5 (SQC), R220.1
RDY: R32.2, U1.2 (RDY)
RW: J6.18, U1.34 (RWB), U4.22 (RWB), U5.22 (RWB), U6.28 (RWB), U7.4 (2A), U7.5 (2B), U7.10 (3B)
SER_CTS: J5.6 (RTS), R35.1, U6.9 (CTSB)
SER_RTS: J5.2 (CTS), U6.8 (RTSB)
SER_RX: J5.4 (TXD), U6.12 (RXD)
SER_TX: J5.5 (RXD), U6.10 (TXD)
USB_5V: J5.3 (VCC), JP2.1
V1_CA2: J6.11, U4.39 (CA2)
V1_CB2: J6.12, U4.19 (CB2)
V1_PA6: J6.9, U4.8 (PA6)
V1_PB6: J6.10, U4.16 (PB6)
V2_CA2: J6.3, U5.39 (CA2)
V2_CB1: J6.7, U5.18 (CB1)
V2_CB2: J6.8, U5.19 (CB2)
V2_PB5: J6.4, U5.15 (PB5)
V2_PB6: J6.5, U5.16 (PB6)
V2_PB7: J6.6, U5.17 (PB7)
VIN: C1.1 (+), D1.1 (K), U12.1 (IN)
VRAW: D1.2 (A), J1.1 (V+)
VREF: C4.1 (+), R4.2, R5.1, R102.1, R202.1, U13.2 (-INA), U13.6 (-INB)
~CS0: U4.23 (CS2B), U10.15 (Y0)
~CS1: U5.23 (CS2B), U10.14 (Y1)
~CS2: U6.3 (CS1B), U10.13 (Y2)
~CS3: J6.13, U10.12 (Y3)
~CS4: J6.14, U10.11 (Y4)
~CS5: J6.19, U10.10 (Y5)
~FWE: JP1.2, U3.31 (~WE)
~IOSEL: U8.2 (1B), U9.8 (Y), U10.4 (~E1)
~IRQ: J6.15, R31.2, U1.4 (IRQB), U4.21 (IRQB), U5.21 (IRQB), U6.26 (IRQB)
~NMI: C30.1, R30.2, SW2.1, U1.6 (NMIB)
~RAMCS: U2.20 (~CE), U8.3 (1Y)
~RD: U2.22 (~OE), U3.24 (~OE), U7.8 (3Y)
~RES: J6.16, SW1.1, U1.40 (RESB), U4.34 (RESB), U5.34 (RESB), U6.4 (RESB), U11.1 (RST)
~ROMCS: U3.22 (~CE), U7.3 (1Y), U8.1 (1A), U9.12 (H)
~WR: JP1.1, U2.27 (~WE), U7.11 (4Y)

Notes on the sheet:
CPU and memory
I/O chips
Address decoding, clock
Reset, interrupts, flash bank, write protect, LEDs
Power
Receive comparators (both radios), I/O header
Radio port 1
Radio port 2
LCD, keyboard, USB serial

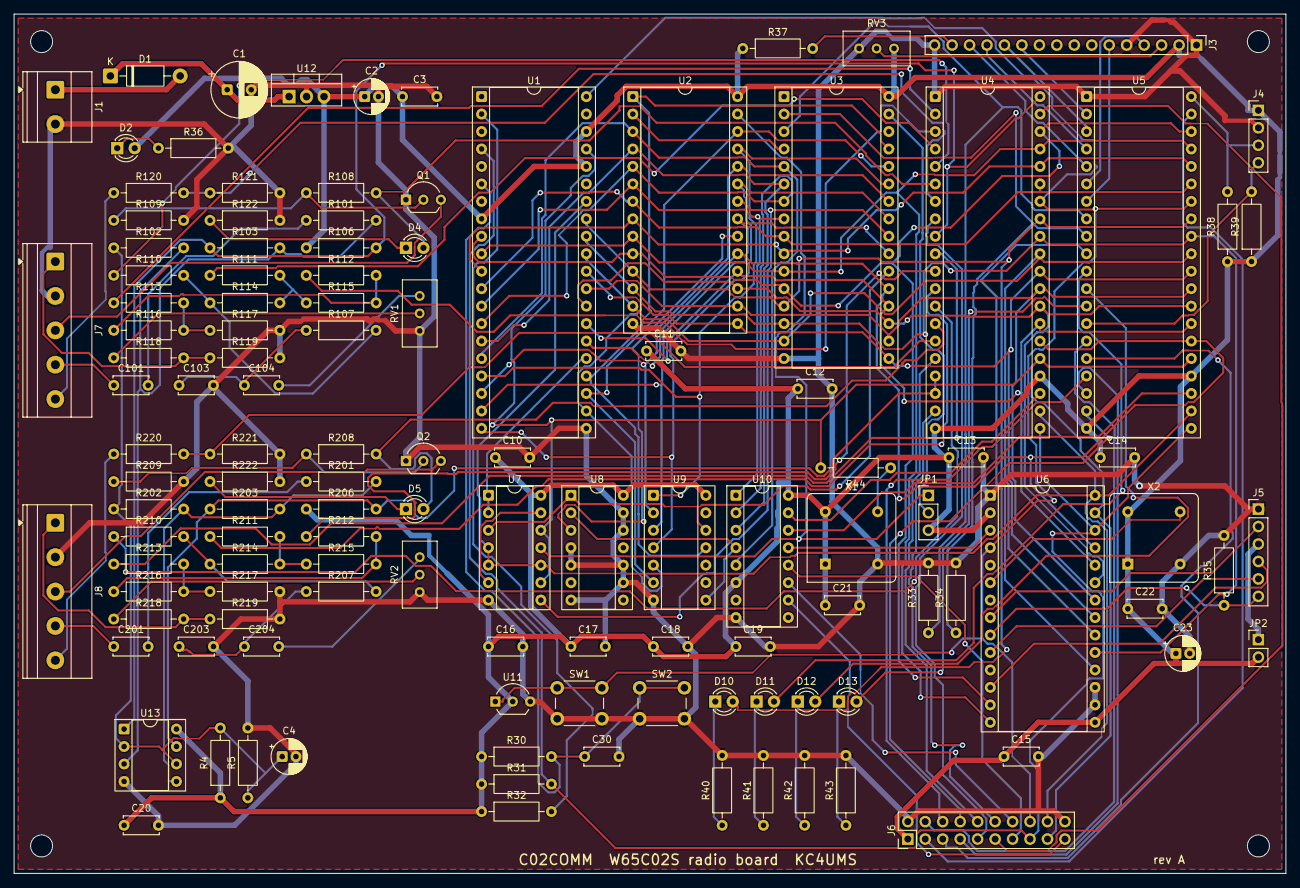
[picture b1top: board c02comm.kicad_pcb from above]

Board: 2 copper layers, 185.0 x 125.0 mm, 125 parts (0 on the bottom side), 130 nets.

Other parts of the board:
H1, H2, H3, H4: M3; MountingHole_3.2mm_M3

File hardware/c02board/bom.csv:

Qty,References,Value,Footprint,Manufacturer,Mfr part,Mouser,Notes
1,C1,100uF 25V,CP_Radial_D8.0mm_P3.50mm,Nichicon,"UVR1H101MPD (50 V, 8 mm, 3.5 mm pitch)",,
3,C2 C4 C23,10uF,CP_Radial_D5.0mm_P2.00mm,Nichicon,"UVR1H100MDD (50 V, 5 mm, 2 mm pitch)",,
15,C3 C10 C11 C12 C13 C14 C15 C16 C17 C18 C19 C20 C21 C22 C30,100nF,C_Disc_D5.0mm_W2.5mm_P5.00mm,KEMET,C330C104K5R5TA,,
4,C101 C104 C201 C204,1uF,C_Disc_D5.0mm_W2.5mm_P5.00mm,KEMET,C330C105K5R5TA,80-C330C105K5R,
2,C103 C203,10nF,C_Disc_D5.0mm_W2.5mm_P5.00mm,KEMET,C330C103K5R5TA,,
1,D1,1N5819,D_DO-41_SOD81_P10.16mm_Horizontal,onsemi,1N5819RLG,863-1N5819RLG,
1,D2,PWR,LED_D3.0mm,Kingbright,WP710A10GD,604-WP710A10GD,"3 mm LED, green"
1,D4,TX1,LED_D3.0mm,Kingbright,WP710A10ID,,"3 mm LED, red"
1,D5,TX2,LED_D3.0mm,Kingbright,WP710A10ID,,"3 mm LED, red"
4,D10 D11 D12 D13,LED,LED_D3.0mm,Kingbright,WP710A10GD,604-WP710A10GD,3 mm LED
1,J1,9-15V,"TerminalBlock_Phoenix_MKDS-1,5-2_1x02_P5.00mm_Horizontal",Phoenix Contact,"1715721 (MKDS 1,5/2)",,"Phoenix MKDS 1,5/2 or any 5 mm screw terminal"
1,J3,LCD 20x4,PinHeader_1x16_P2.54mm_Vertical,Amphenol,"68000-136HLF (1x36 strip, cut to length)",649-68000-136HLF,
1,J4,PS/2 KBD,PinHeader_1x04_P2.54mm_Vertical,,cut from the strip on the J3 line,,
1,J5,USB-SERIAL,PinHeader_1x06_P2.54mm_Vertical,,cut from the strip on the J3 line,,
1,J6,I/O,PinHeader_2x10_P2.54mm_Vertical,any,"2x10 pin header, 2.54 mm",,
1,J7,RADIO 1,"TerminalBlock_Phoenix_MKDS-1,5-5_1x05_P5.00mm_Horizontal",Phoenix Contact,"1715750 (MKDS 1,5/5)",,5 mm 5-way screw terminal
1,J8,RADIO 2,"TerminalBlock_Phoenix_MKDS-1,5-5_1x05_P5.00mm_Horizontal",Phoenix Contact,"1715750 (MKDS 1,5/5)",,5 mm 5-way screw terminal
1,JP1,FLASH WE,PinHeader_1x03_P2.54mm_Vertical,,cut from the strip on the J3 line,,
1,JP2,USB PWR,PinHeader_1x02_P2.54mm_Vertical,,cut from the strip on the J3 line,,
2,Q1 Q2,2N7000,TO-92_Inline_Wide,onsemi,2N7000,512-2N7000,2N7000 (TO-92)
16,R4 R33 R34 R35 R101 R106 R114 R115 R116 R120 R201 R206 R214 R215 R216 R220,10k,R_Axial_DIN0207_L6.3mm_D2.5mm_P10.16mm_Horizontal,Yageo,MFR-25FBF52-10K,603-MFR-25FBF52-10K,
1,R5,6.8k,R_Axial_DIN0207_L6.3mm_D2.5mm_P10.16mm_Horizontal,Yageo,MFR-25FBF52-6K8,603-MFR-25FBF52-6K8,
3,R30 R31 R32,3.3k,R_Axial_DIN0207_L6.3mm_D2.5mm_P10.16mm_Horizontal,Yageo,MFR-25FBF52-3K3,603-MFR-25FBF52-3K3,
7,R36 R40 R41 R42 R43 R122 R222,1k,R_Axial_DIN0207_L6.3mm_D2.5mm_P10.16mm_Horizontal,Yageo,MFR-25FBF52-1K,603-MFR-25FBF52-1K,
2,R37 R44,33,R_Axial_DIN0207_L6.3mm_D2.5mm_P10.16mm_Horizontal,Yageo,MFR-25FBF52-33R,603-MFR-25FBF52-33R,
4,R38 R39 R107 R207,4.7k,R_Axial_DIN0207_L6.3mm_D2.5mm_P10.16mm_Horizontal,Yageo,MFR-25FBF52-4K7,603-MFR-25FBF52-4K7,
6,R102 R109 R118 R202 R209 R218,100k,R_Axial_DIN0207_L6.3mm_D2.5mm_P10.16mm_Horizontal,Yageo,MFR-25FBF52-100K,603-MFR-25FBF52-100K,
2,R103 R203,1M,R_Axial_DIN0207_L6.3mm_D2.5mm_P10.16mm_Horizontal,Yageo,MFR-25FBF52-1M,603-MFR-25FBF52-1M,
2,R108 R208,100,R_Axial_DIN0207_L6.3mm_D2.5mm_P10.16mm_Horizontal,Yageo,MFR-25FBF52-100R,603-MFR-25FBF52-100R,
10,R110 R111 R112 R113 R117 R210 R211 R212 R213 R217,20k,R_Axial_DIN0207_L6.3mm_D2.5mm_P10.16mm_Horizontal,Yageo,MFR-25FBF52-20K,603-MFR-25FBF52-20K,
2,R119 R219,2.2k,R_Axial_DIN0207_L6.3mm_D2.5mm_P10.16mm_Horizontal,Yageo,MFR-25FBF52-2K2,603-MFR-25FBF52-2K2,
3,RV1 RV2 RV3,10k,Potentiometer_Bourns_3296W_Vertical,Bourns,3296W-1-103LF,652-3296W-1-103LF,
1,SW1,RESET,SW_PUSH_6mm,TE Connectivity,1825910-6,650-1825910-6,6 mm tactile switch
1,SW2,NMI,SW_PUSH_6mm,TE Connectivity,1825910-6,650-1825910-6,6 mm tactile switch
1,U1,W65C02S6TPG-14,DIP-40_W15.24mm_Socket,WDC,W65C02S6TPG-14,955-W65C02S6TPG-14,WDC W65C02S6TPG-14
1,U2,AS6C62256-55PCN,DIP-28_W15.24mm_Socket,Alliance Memory,AS6C62256-55PCN,,Alliance AS6C62256-55PCN
1,U3,SST39SF010A-70-4C-PHE,DIP-32_W15.24mm_Socket,Microchip,SST39SF010A-70-4C-PHE,804-39SF010A7CPHE,Microchip SST39SF010A-70-4C-PHE
2,U4 U5,W65C22N6TPG-14,DIP-40_W15.24mm_Socket,WDC,W65C22N6TPG-14,955-W65C22N6TPG-14,WDC W65C22N6TPG-14 (N = open-drain IRQ)
1,U6,W65C51N6TPG-14,DIP-28_W15.24mm_Socket,WDC,W65C51N6TPG-14,,WDC W65C51N6TPG-14
2,U7 U8,74HC00,DIP-14_W7.62mm_Socket,Texas Instruments,SN74HC00N,595-SN74HC00N,74HC00 (TI SN74HC00N)
1,U9,74HC30,DIP-14_W7.62mm_Socket,Texas Instruments,SN74HC30N,,74HC30 (TI SN74HC30N)
1,U10,74HC138,DIP-16_W7.62mm_Socket,Texas Instruments,SN74HC138N,595-SN74HC138N,74HC138 (TI SN74HC138N)
1,U11,DS1813-10+,TO-92_Inline_Wide,Analog Devices,DS1813-10+,700-DS1813-10+,Analog Devices DS1813-10+
1,U12,LM7805,TO-220-3_Vertical,Texas Instruments,LM7805CT/NOPB,926-LM7805CT/NOPB,LM7805 (TO-220) with a clip-on heatsink
1,U13,LM393,DIP-8_W7.62mm_Socket,Texas Instruments,LM393P,595-LM393P,LM393P (TI) or any LM393 DIP-8
1,X1,3.6864MHz,Oscillator_DIP-8,CTS,MXO45HS-3C-3M686400,774-MXO45HS-3C-3.6,any 5 V HCMOS half-size (8-pin DIP) can
1,X2,1.8432MHz,Oscillator_DIP-8,CTS,MXO45HS-3C-1M843200,,any 5 V HCMOS half-size (8-pin DIP) can
3,U1 U4 U5,socket DIP-40 0.6 in,,,,,not on the PCB
2,U2 U6,socket DIP-28 0.6 in,,,,,not on the PCB
1,U3,socket DIP-32 0.6 in (or a ZIF),,,,,not on the PCB
3,U7 U8 U9,socket DIP-14 0.3 in,,,,,not on the PCB
1,U10,socket DIP-16 0.3 in,,,,,not on the PCB
3,U13 X1 X2,socket DIP-8 0.3 in,,,,,not on the PCB
1,U12,TO-220 clip-on heatsink,,,,,not on the PCB
2,JP1 JP2,jumper shunt 2.54 mm,,,,,not on the PCB
1,J3,"20x4 HD44780 LCD, 5 V",,,,,not on the PCB
1,J4,"PS/2 socket breakout, 5 V",,,,,not on the PCB
1,J5,"USB-serial module, FTDI pinout, 5 V",,,,,not on the PCB
